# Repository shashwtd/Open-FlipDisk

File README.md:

# Open-FlipDisc

an open source 5x5 flip-dot display module built around custom electromagnetic flip discs, a Raspberry Pi Pico 2 W, and a custom driver PCB.

I started this because small flip-dot modules are hard to find, and the polished commercial options from companies like [AlfaZeta](https://flipdots.com/en/home/) are too expensive for this project. this repository has all the work ive done on this project in my attempt to make my own flip dot display.. it also contains a PCB which can be used to drive the flipdots individually

### current design
- 5x5 flip-dot matrix, 25 individually controlled dots
- Raspberry Pi Pico 2 W controller
- TB6612FNG motor drivers for coil driving
- 74HC595 shift registers for expanding control lines
- 12V input with onboard 5V regulation
- JLCPCB SMD assembly for the SMD parts
- Through-hole parts, Pico, regulator, connectors, and mechanical hardware installed manually

here's how the PCB looks:

some CAD renders for module, made in fusion:

this is my first rough 3D printed draft 3x3 grid:

the bill of materials for this project can be found [here](BOM.csv)

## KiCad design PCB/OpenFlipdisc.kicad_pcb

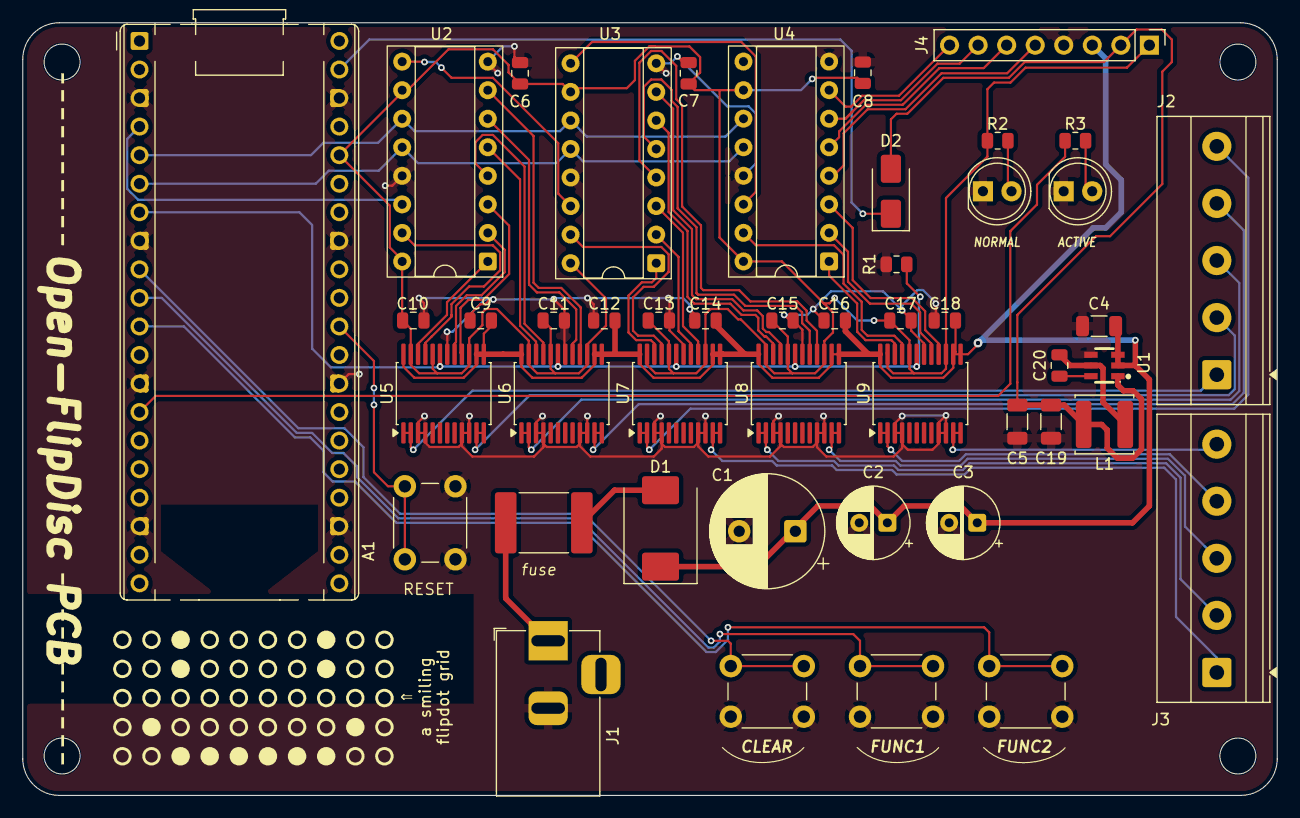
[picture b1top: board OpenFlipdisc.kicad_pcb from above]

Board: 2 copper layers, 111.6 x 68.8 mm, 51 parts (0 on the bottom side), 56 nets.

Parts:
A1: RaspberryPi_Pico_W; RaspberryPi_Pico_Common_THT
C1: 1000uF; CP_Radial_D10.0mm_P5.00mm
C2, C3: 100uF; CP_Radial_D6.3mm_P2.50mm
C4: 10uF; C_1206_3216Metric
C5, C19: 22uF; C_1206_3216Metric
C6, C7, C8, C9, C10, C11, C12, C13, C14, C15, C16, C17, C18: 0.1uF; C_0805_2012Metric
C20: 100nF; C_0805_2012Metric
D1: SS34; D_SMC
D2: SS14; D_SMA
D3: D_PWR (green); LED_D5.0mm
D4: D_ACT (red); LED_D5.0mm
F1: Fuse T2A; Fuse_2920_7451Metric
H1, H2, H3, H4: MountingHole; MountingHole_3.2mm_M3
J1: Barrel_Jack; BarrelJack_Horizontal
J2, J3: Screw_Terminal_01x05; TerminalBlock_Phoenix_MKDS-1,5-5-5.08_1x05_P5.08mm_Horizont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
J4: Conn_01x08; PinHeader_1x08_P2.54mm_Vertical
L1: 4.7uH; L_Sunlord_SWPA5040S
R1: 10k; R_0805_2012Metric
R2, R3: 330R; R_0805_2012Metric
SW1: CLEAR; SW_PUSH_6mm
SW2: FUNC1; SW_PUSH_6mm
SW3: FUNC2; SW_PUSH_6mm
SW4: RESET; SW_PUSH_6mm
U1: AP63205WU-7; TSOT-23-6_L2.9-W1.6-P0.95-LS2.8-BL
U2, U3, U4: 74HC595; DIP-16_W7.62mm_Socket
U5, U6, U7, U8, U9: TB6612FNG; SSOP-24_5.3x8.2mm_P0.65mm

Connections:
+3V3: A1.36 (3V3), C6.1, C7.1, C8.1, C10.1, C11.1, C13.1, C15.1, C17.1, J4.1, R2.2, U2.10 (~SRCLR), U2.16 (VCC), U3.10 (~SRCLR), U3.16 (VCC), U4.10 (~SRCLR), U4.16 (VCC), U5.15 (PWMB), U5.20 (VCC), U5.23 (PWMA), U6.15 (PWMB), U6.20 (VCC), U6.23 (PWMA), U7.15 (PWMB), U7.20 (VCC), U7.23 (PWMA), U8.15 (PWMB), U8.20 (VCC), U8.23 (PWMA), U9.15 (PWMB), U9.20 (VCC), U9.23 (PWMA)
+5V: C5.1, C19.1, D2.2 (A), J4.2, L1.2, U1.1 (FB)
C0: J3.1, U7.11 (BO1), U7.12 (BO1)
C1: J3.2, U8.1 (AO1), U8.2 (AO1)
C2: J3.3, U8.11 (BO1), U8.12 (BO1)
C3: J3.4, U9.1 (AO1), U9.2 (AO1)
C4: J3.5, U9.11 (BO1), U9.12 (BO1)
DRV1_AIN1: U2.15 (QA), U5.21 (AIN1)
DRV1_AIN2: U2.1 (QB), U5.22 (AIN2)
DRV1_BIN1: U2.2 (QC), U5.17 (BIN1)
DRV1_BIN2: U2.3 (QD), U5.16 (BIN2)
DRV2_AIN1: U2.4 (QE), U6.21 (AIN1)
DRV2_AIN2: U2.5 (QF), U6.22 (AIN2)
DRV2_BIN1: U2.6 (QG), U6.17 (BIN1)
DRV2_BIN2: U2.7 (QH), U6.16 (BIN2)
DRV3_AIN1: U3.15 (QA), U7.21 (AIN1)
DRV3_AIN2: U3.1 (QB), U7.22 (AIN2)
DRV3_BIN1: U3.2 (QC), U7.17 (BIN1)
DRV3_BIN2: U3.3 (QD), U7.16 (BIN2)
DRV4_AIN1: U3.7 (QH), U8.21 (AIN1)
DRV4_AIN2: U3.6 (QG), U8.22 (AIN2)
DRV4_BIN1: U3.5 (QF), U8.17 (BIN1)
DRV4_BIN2: U3.4 (QE), U8.16 (BIN2)
DRV5_AIN1: U4.15 (QA), U9.21 (AIN1)
DRV5_AIN2: U4.1 (QB), U9.22 (AIN2)
DRV5_BIN1: U4.2 (QC), U9.17 (BIN1)
DRV5_BIN2: U4.3 (QD), U9.16 (BIN2)
GND: A1.3 (GND), A1.8 (GND), A1.13 (GND), A1.18 (GND), A1.23 (GND), A1.28 (GND), A1.33 (AGND), A1.38 (GND), C1.2, C2.2, C3.2, C4.2, C5.2, C6.2, C7.2, C8.2, C9.2, C10.2, C11.2, C12.2, C13.2, C14.2, C15.2, C16.2, C17.2, C18.2, C19.2, D3.1 (K), D4.1 (K), J1.2, J4.4, R1.2, SW1.2, SW2.2, SW3.2, SW4.1, U1.4 (GND), U2.8 (GND), U2.13 (~OE), U3.8 (GND), U3.13 (~OE), U4.8 (GND), U4.13 (~OE), U5.3 (PGND1), U5.4 (PGND1), U5.9 (PGND2), U5.10 (PGND2), U5.18 (GND), U6.3 (PGND1), U6.4 (PGND1), U6.9 (PGND2), U6.10 (PGND2), U6.18 (GND), U7.3 (PGND1), U7.4 (PGND1), U7.9 (PGND2), U7.10 (PGND2), U7.18 (GND), U8.3 (PGND1), U8.4 (PGND1), U8.9 (PGND2), U8.10 (PGND2), U8.18 (GND), U9.3 (PGND1), U9.4 (PGND1), U9.9 (PGND2), U9.10 (PGND2), U9.18 (GND)
GP06: A1.9 (GPIO6), SW1.1
GP07: A1.10 (GPIO7), SW2.1
GP08: A1.11 (GPIO8), SW3.1
GP10: A1.14 (GPIO10), R3.1
unnamed: A1.30 (RUN), SW4.2
unnamed: A1.39 (VSYS), D2.1 (K)
unnamed: D1.2 (A), F1.2
unnamed: D3.2 (A), R2.1
unnamed: D4.2 (A), R3.2
unnamed: F1.1, J1.1
unnamed: C20.1, U1.6 (BST)
unnamed: C20.2, L1.1, U1.5 (SW)
unnamed: U2.9 (QH'), U3.14 (SER)
unnamed: U3.9 (QH'), U4.14 (SER)
R0: J2.1, U5.1 (AO1), U5.2 (AO1)
R1: J2.2, U5.11 (BO1), U5.12 (BO1)
R2: J2.3, U6.1 (AO1), U6.2 (AO1)
R3: J2.4, U6.11 (BO1), U6.12 (BO1)
R4: J2.5, U7.1 (AO1), U7.2 (AO1)
SR_CLK: A1.5 (GPIO3), U2.11 (SRCLK), U3.11 (SRCLK), U4.11 (SRCLK)
SR_DATA: A1.4 (GPIO2), U2.14 (SER)
SR_LATCH: A1.6 (GPIO4), U2.12 (RCLK), U3.12 (RCLK), U4.12 (RCLK)
STBY: A1.7 (GPIO5), R1.1, U5.19 (STBY), U6.19 (STBY), U7.19 (STBY), U8.19 (STBY), U9.19 (STBY)
TP1: J4.5, U4.4 (QE)
TP2: J4.6, U4.5 (QF)
TP3: J4.7, U4.6 (QG)
TP4: J4.8, U4.7 (QH)
VM: C1.1, C2.1, C3.1, C4.1, C9.1, C12.1, C14.1, C16.1, C18.1, D1.1 (K), J4.3, U1.2 (EN), U1.3 (VIN), U5.13 (VM2), U5.14 (VM3), U5.24 (VM1), U6.13 (VM2), U6.14 (VM3), U6.24 (VM1), U7.13 (VM2), U7.14 (VM3), U7.24 (VM1), U8.13 (VM2), U8.14 (VM3), U8.24 (VM1), U9.13 (VM2), U9.14 (VM3), U9.24 (VM1)

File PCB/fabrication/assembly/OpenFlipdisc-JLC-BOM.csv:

Designator,Comment,Footprint,LCSC Part #
C1,1000uF 25V,CP_Radial_D10.0mm_P5.00mm,C88727
C2,100uF 25V,CP_Radial_D6.3mm_P2.50mm,C108856
C3,100uF 25V,CP_Radial_D6.3mm_P2.50mm,C108856
C4,10uF,C_1206_3216Metric,C13585
C5,22uF,C_1206_3216Metric,C12891
C6,0.1uF,C_0805_2012Metric,C49678
C7,0.1uF,C_0805_2012Metric,C49678
C8,0.1uF,C_0805_2012Metric,C49678
C9,0.1uF,C_0805_2012Metric,C49678
C10,0.1uF,C_0805_2012Metric,C49678
C11,0.1uF,C_0805_2012Metric,C49678
C12,0.1uF,C_0805_2012Metric,C49678
C13,0.1uF,C_0805_2012Metric,C49678
C14,0.1uF,C_0805_2012Metric,C49678
C15,0.1uF,C_0805_2012Metric,C49678
C16,0.1uF,C_0805_2012Metric,C49678
C17,0.1uF,C_0805_2012Metric,C49678
C18,0.1uF,C_0805_2012Metric,C49678
D1,SS34,D_SMC,C154551
D2,SS14,D_SMA,C2480
D3,LED 5mm green,LED_D5.0mm,C2895548
F1,PTC 2A hold,Fuse_2920_7451Metric,C369176
J1,Barrel_Jack 5.5x2.1,BarrelJack_Horizontal,C381116
J2,Screw terminal 1x05 5.08mm,TerminalBlock_Phoenix_MKDS-1.5-5-5.08_1x05,C2961928
J3,Screw terminal 1x05 5.08mm,TerminalBlock_Phoenix_MKDS-1.5-5-5.08_1x05,C2961928
J4,PinHeader 1x08 2.54mm,PinHeader_1x08_P2.54mm_Vertical,C2894950
R1,10k,R_0805_2012Metric,C17414
R2,330R,R_0805_2012Metric,C17630
R3,330R,R_0805_2012Metric,C17630
U2,74HC595 DIP-16,DIP-16_W7.62mm_Socket,C78711
U3,74HC595 DIP-16,DIP-16_W7.62mm_Socket,C78711
U4,74HC595 DIP-16,DIP-16_W7.62mm_Socket,C78711
U5,TB6612FNG,SSOP-24_5.3x8.2mm_P0.65mm,C88224
U6,TB6612FNG,SSOP-24_5.3x8.2mm_P0.65mm,C88224
U7,TB6612FNG,SSOP-24_5.3x8.2mm_P0.65mm,C88224
U8,TB6612FNG,SSOP-24_5.3x8.2mm_P0.65mm,C88224
U9,TB6612FNG,SSOP-24_5.3x8.2mm_P0.65mm,C88224

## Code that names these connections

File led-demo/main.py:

# Open-FlipDisc: 3x3 LED test grid on the driver board.
#
# LEDs stand in for the flip-disc coils. The board drives every row and column
# line high (12 V), low (GND) or floating, exactly as it would for a coil, and
# lights one row at a time fast enough that the whole grid looks steady.
#
# Runs on the Pico 2 W with MicroPython. Talks to controller.html over USB.
# Commands (one per line):
#   F<25 x 0/1>  set the whole 5x5 frame, rows R0-R4, columns C0-C4
#   C            clear
#   ?            print the current frame
# Buttons: CLEAR clears, FUNC1 shows the next pattern, FUNC2 starts/stops a chase.

import select
import sys
import time
from machine import Pin

# ---- Board pins (from the PCB) ----
SR_DATA = Pin(2, Pin.OUT, value=0)   # 74HC595 SER, first chip (U2)
SR_CLK = Pin(3, Pin.OUT, value=0)    # SRCLK, all three 74HC595s
SR_LATCH = Pin(4, Pin.OUT, value=0)  # RCLK, all three 74HC595s
STBY = Pin(5, Pin.OUT, value=0)      # TB6612 STBY (10k pull-down: drivers off until high)
ACT_LED = Pin(10, Pin.OUT, value=0)  # red ACTIVE LED
BUTTONS = [Pin(6, Pin.IN, Pin.PULL_UP),   # CLEAR
           Pin(7, Pin.IN, Pin.PULL_UP),   # FUNC1
           Pin(8, Pin.IN, Pin.PULL_UP)]   # FUNC2

# Each matrix line is output 1 of one TB6612 channel. The pairs are the
# (IN1, IN2) bit positions in the 24-bit shift-register word:
# U2 = bits 0-7 (QA-QH), U3 = bits 8-15, U4 = bits 16-23.
ROWS = [(0, 1), (2, 3), (4, 5), (6, 7), (8, 9)]            # R0-R4 = J2 pins 1-5
COLS = [(10, 11), (15, 14), (13, 12), (16, 17), (18, 19)]  # C0-C4 = J3 pins 1-5

# Lines wired to the breadboard. The other lines are never driven.
ACTIVE_ROWS = [2, 3, 4]  # R2, R3, R4 = J2 pins 3, 4, 5
ACTIVE_COLS = [0, 1, 2]  # C0, C1, C2 = J3 pins 1, 2, 3

ROW_TIME_US = 1500  # time each row stays lit per scan
CHASE_MS = 400      # FUNC2 chase speed: bigger = slower
ACT_FLASH_MS = 150  # how long the red ACTIVE LED flashes on each change
DEBOUNCE_MS = 250

PATTERNS = ["111111111", "101010101", "010111010", "111101111", "010101010", "000010000"]
RING = [(0, 0), (0, 1), (0, 2), (1, 2), (2, 2), (2, 1), (2, 0), (1, 0)]

frame = [[0] * 5 for _ in range(5)]


# A line whose IN1 and IN2 bits are both 0 floats (TB6612 "stop").
def high(word, line):
    return word | (1 << line[0])  # IN1=1, IN2=0: output at 12 V


def low(word, line):
    return word | (1 << line[1])  # IN1=0, IN2=1: output at GND


def build_words():
    """One shift-register word per active row: that row high, its lit columns low."""
    words = []
    for r in ACTIVE_ROWS:
        word = 0
        lit = [c for c in ACTIVE_COLS if frame[r][c]]
        if lit:
            word = high(word, ROWS[r])
            for c in lit:
                word = low(word, COLS[c])
        words.append(word)
    return words


def shift_out(word):
    data = SR_DATA.value
    clk = SR_CLK.value
    for bit in range(23, -1, -1):  # first bit ends up in U4 QH, last in U2 QA
        data((word >> bit) & 1)
        clk(1)
        clk(0)
    SR_LATCH.value(1)
    SR_LATCH.value(0)


def clear():
    for row in frame:
        for c in range(5):
            row[c] = 0


def show_3x3(bits):
    for i, r in enumerate(ACTIVE_ROWS):
        for j, c in enumerate(ACTIVE_COLS):
            frame[r][c] = 1 if bits[i * 3 + j] == "1" else 0


def frame_string():
    return "F" + "".join(str(frame[r][c]) for r in range(5) for c in range(5))


def handle(cmd):
    """Apply one command. Returns True if the frame changed."""
    # No "OK" replies: if nothing reads them, USB writes can stall the scan.
    if cmd.startswith("F") and len(cmd) == 26 and all(ch in "01" for ch in cmd[1:]):
        for i in range(25):
            frame[i // 5][i % 5] = 1 if cmd[1 + i] == "1" else 0
        return True
    if cmd == "C":
        clear()
        return True
    if cmd == "?":
        print(frame_string())
        return False
    print("ERR " + cmd)
    return False


def main():
    poll = select.poll()
    poll.register(sys.stdin, select.POLLIN)
    rx = ""
    last_press = [0, 0, 0]
    was_down = [False, False, False]
    pattern = -1
    chasing = False
    chase_step = 0
    last_chase = time.ticks_ms()
    act_until = 0

    shift_out(0)   # every line floating before the drivers wake up
    STBY.value(1)
    print("OPENFLIPDISC READY rows R2-R4, cols C0-C2")
    words = build_words()
    row = 0
    try:
        while True:
            shift_out(words[row % len(words)])
            row += 1
            changed = False
            now = time.ticks_ms()

            while poll.poll(0):  # commands from controller.html
                ch = sys.stdin.read(1)
                if ch in ("\n", "\r"):
                    if rx:
                        if handle(rx.strip()):
                            changed = True
                            chasing = False
                        rx = ""
                else:
                    rx = (rx + ch)[-40:]

            for i, btn in enumerate(BUTTONS):  # buttons on the board
                down = btn.value() == 0
                if down and not was_down[i] and time.ticks_diff(now, last_press[i]) > DEBOUNCE_MS:
                    last_press[i] = now
                    changed = True
                    if i == 0:
                        clear()
                        chasing = False
                    elif i == 1:
                        pattern = (pattern + 1) % len(PATTERNS)
                        show_3x3(PATTERNS[pattern])
                        chasing = False
                    else:
                        chasing = not chasing
                        clear()
                was_down[i] = down

            if chasing and time.ticks_diff(now, last_chase) > CHASE_MS:
                last_chase = now
                i, j = RING[chase_step % len(RING)]
                chase_step += 1
                clear()
                frame[ACTIVE_ROWS[i]][ACTIVE_COLS[j]] = 1
                changed = True

            if changed:
                words = build_words()
                ACT_LED.value(1)  # red ACTIVE LED blinks on every change
                act_until = time.ticks_add(now, ACT_FLASH_MS)
            elif ACT_LED.value() and time.ticks_diff(now, act_until) > 0:
                ACT_LED.value(0)

            time.sleep_us(ROW_TIME_US)
    finally:
        shift_out(0)
        STBY.value(0)
        ACT_LED.value(0)


if __name__ == "__main__":
    main()

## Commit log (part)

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2026-06-14 repo push wohoooo
